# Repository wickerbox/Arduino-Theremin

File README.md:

# Arduino Theremin v1

Playing music by waving your hands over a rangefinder for pitch and pressing capacitive sense pads for key.

## Instructions

1. Program the Arduino Uno
1. To use it, the Uno needs some sort of power, 9V or 5V or whatever.
1. Press the 'reset' button. The red and green lights will blink.
1. The switch normally sits in the 'OFF' position.
1. Flip the switch to the RECORD position to play and record a tune.
1. Move one hand vertically between 1 and about 10 inches above the rangefinder.
1. Use the other hand to press the capacitive sense pads to choose a key.
1. When you're done with a tune, flip the switch back to OFF.
1. When you want to play back the tune, flip the switch to PLAYBACK.
1. The tune will play once through. 
1. To play it again, flip the switch to OFF and then to PLAYBACK.
1. To record a new tune, flip the switch to RECORD, which erases the old tune.

## Bill of Materials

I've <a href="https://oshpark.com/shared_projects/u5dTU3Mx">shared the boards at OSH Park</a>. You can buy a set of three for $29.50. 

|Refdes|Qty|Description|Digikey|
|------|---|-----------|-------|
|J1|1|CONN HEADER FEMALE .100" SNGL STR 8POS|952-1823-ND|
|LED1|1|LED RED DIFF 5MM ROUND T/H|1125-1188-ND|
|LED2|1|LED GRN DIFF 5MM ROUND T/H|1125-1184-ND|
|R1,R2|2|RES 220 OHM 1/4W 5% CF MINI|S220QCT-ND|
|R3,R4|2|RES 10K OHM 1/4W 5% CF MINI|S10KQCT-ND|
|RV1|1|POT 10K OHM 1/5W PLASTIC LINEAR|987-1301-ND|
|SP1|1|SPEAKER 8 OHM .25W 23MM ROUND|458-1124-ND|
|SW1|1|SWITCH TACTILE SPST-NO 0.05A 24V|SW400-ND|
|SW2|1|SWITCH TOGGLE SPDT 5A 120V|EG2377-ND|
|U1|1|CONN HEADER MALE .100" SNGL STR 40POS|S1012EC-40-ND|

The best way to place U1 is to buy one 40-position header is the cheapest option (about $0.50) and snap it apart into the sections you need.

|Refdes|Qty|Description|Adafruit|
|------|---|-----------|--------|
|P1|1|Maxbotix Ultrasonic Rangefinder LV-EZ1|Product 172|

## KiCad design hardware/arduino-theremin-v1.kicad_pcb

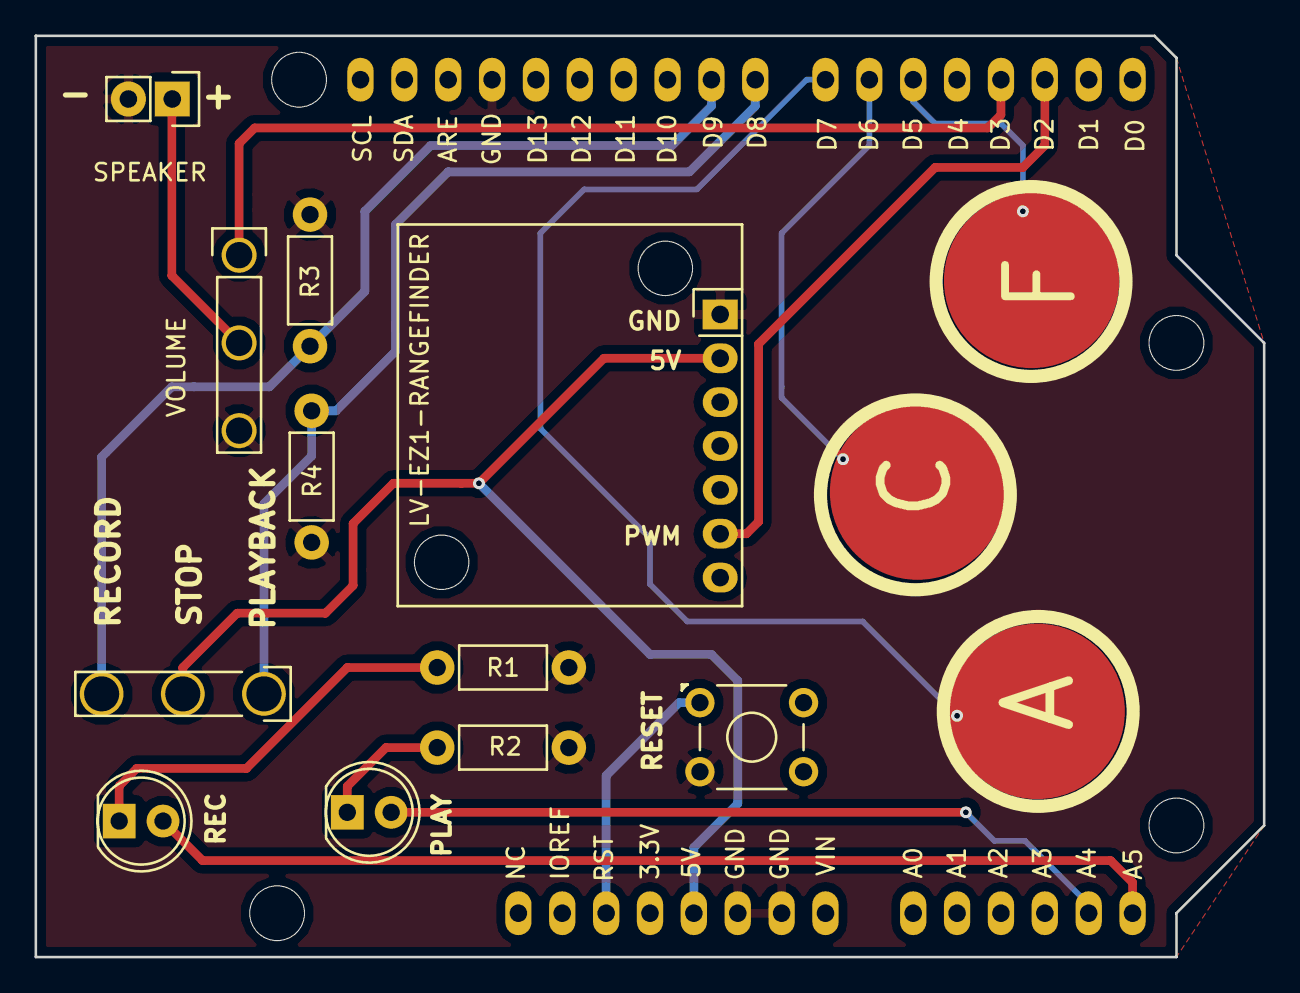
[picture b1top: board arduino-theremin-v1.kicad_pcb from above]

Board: 2 copper layers, 71.1 x 53.3 mm, 15 parts (0 on the bottom side), 15 nets.

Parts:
A: KEY1; CAPSENSE-CIRCLE-D10
C: KEY2; CAPSENSE-CIRCLE-D10
F: KEY3; CAPSENSE-CIRCLE-D10
LV-EZ1-RANGEFINDER: LV-EZ1-RANGEFINDER; LV_EZ1_Rangefinder
PLAY: PLAYBACK; LED-5MM-2PIN
R1, R2: 220; Resistor_Horizontal_RM7mm
R3, R4: 10K; Resistor_Horizontal_RM7mm
REC: RECORD; LED-5MM-2PIN
RESET: B3F-1000; SW-B3F-10XX
S1: 100SP3 ON-OFF-ON; SW-100SP3
SPEAKER: 8 OHM; OSTVN02A150
U1: ARDUINO-UNO-SHIELD; ARDU-UNOSHIELD
VOLUME: 10K; P160-TRIMPOT

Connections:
+5V: LV-EZ1-RANGEFINDER.2, S1.2, U1.5V
/A4_PLAYBACK_LED: PLAY.2, U1.A4
/A5_RECORD_LED: REC.2, U1.A5
/D2_PWM: LV-EZ1-RANGEFINDER.6, U1.D2
/D3_DIG_SPEAKER_OUT: U1.D3, VOLUME.1
/D5_KEY3: F.1, U1.D5
/D6_KEY2: C.1, U1.D6
/D7_KEY1: A.1, U1.D7
/D8_BTN_PLAYBACK: R4.1, S1.1, U1.D8
/D9_BTN_RECORD: R3.1, S1.3, U1.D9
/RESET: RESET.1, U1.RST
GND: LV-EZ1-RANGEFINDER.1, R1.2, R2.2, R3.2, R4.2, RESET.3, SPEAKER.2, U1.GND1, U1.GND2, U1.GND3, VOLUME.3
unnamed: R1.1, REC.1
unnamed: PLAY.1, R2.1
unnamed: SPEAKER.1, VOLUME.2

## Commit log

2013-11-30 Just messing around on a Saturday afternoon.
2013-11-30 Added Arduino sketch.
2013-12-01 Cleaning up repo.
2016-03-09 Trying out version 1.1 footprint fix.
2016-03-09 Removed extra example code.
2016-04-30 Add gitignore.
2016-04-30 v1.3, based on wickerlib, fixes the reversed rangefinder. Ordered from OSH Park.
2016-04-30 Updated BOM and preview image for v1.3.
2016-05-15 Reorg. Remove ancient code. Change default KiCad settings.
2016-05-15 Ported Arduino Theremin to use Wickerlib.
2016-05-19 Added text on schematic to indicate A, C, F keys.
2016-05-19 Added inputs, outputs, tune vars, and basic blinky test sketch.
2016-05-19 Looks like Rec/PB pins are backwards in schematic. Fixed in code, added states to sketch.
2016-05-19 Got the distance-to-note correlation figured out.
2016-05-19 Setting the key based on cap sense press.
2016-05-19 You can now play it. Major cleanup of code. Can't record yet.
2016-05-19 Record and Playback work just fine. I think we're feature complete.
2016-05-19 Updated board file to match correct names for D8 and D9 PLAYBACK and RECORD. All done.
2016-05-20 Finished writeup, added photo.
2016-05-20 Added CERN license.

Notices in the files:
hardware/arduino-theremin-v1.kicad_pcb:
Released under the CERN Open Hardware License v1.2
